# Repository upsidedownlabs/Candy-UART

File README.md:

# Candy UART

Candy size USB to UART bridge.

#### CH340C Candy

| Front              |  Back |
| :-------------------------: | :-------------------------: |
|   |  |

| Dimensions              |  Schematic |
| :-------------------------: | :-------------------------: |
| 24.00 x 17.00 mm  |  |

#### FT232RQ Candy

| Front              |  Back |
| :-------------------------: | :-------------------------: |
|   |  |

| Dimensions              |  Schematic |
| :-------------------------: | :-------------------------: |
| 24.00 x 17.00 mm  |  |

## License
#### Hardware
CERN Open Hardware License Version 2 - Strongly Reciprocal ([CERN-OHL-S-2.0](https://spdx.org/licenses/CERN-OHL-S-2.0.html)).

#### Software
MIT open source [license](http://opensource.org/licenses/MIT).

#### Documentation:
<br />This work is licensed under a <a rel="license" href="http://creativecommons.org/licenses/by/4.0/">Creative Commons Attribution 4.0 International License</a>.

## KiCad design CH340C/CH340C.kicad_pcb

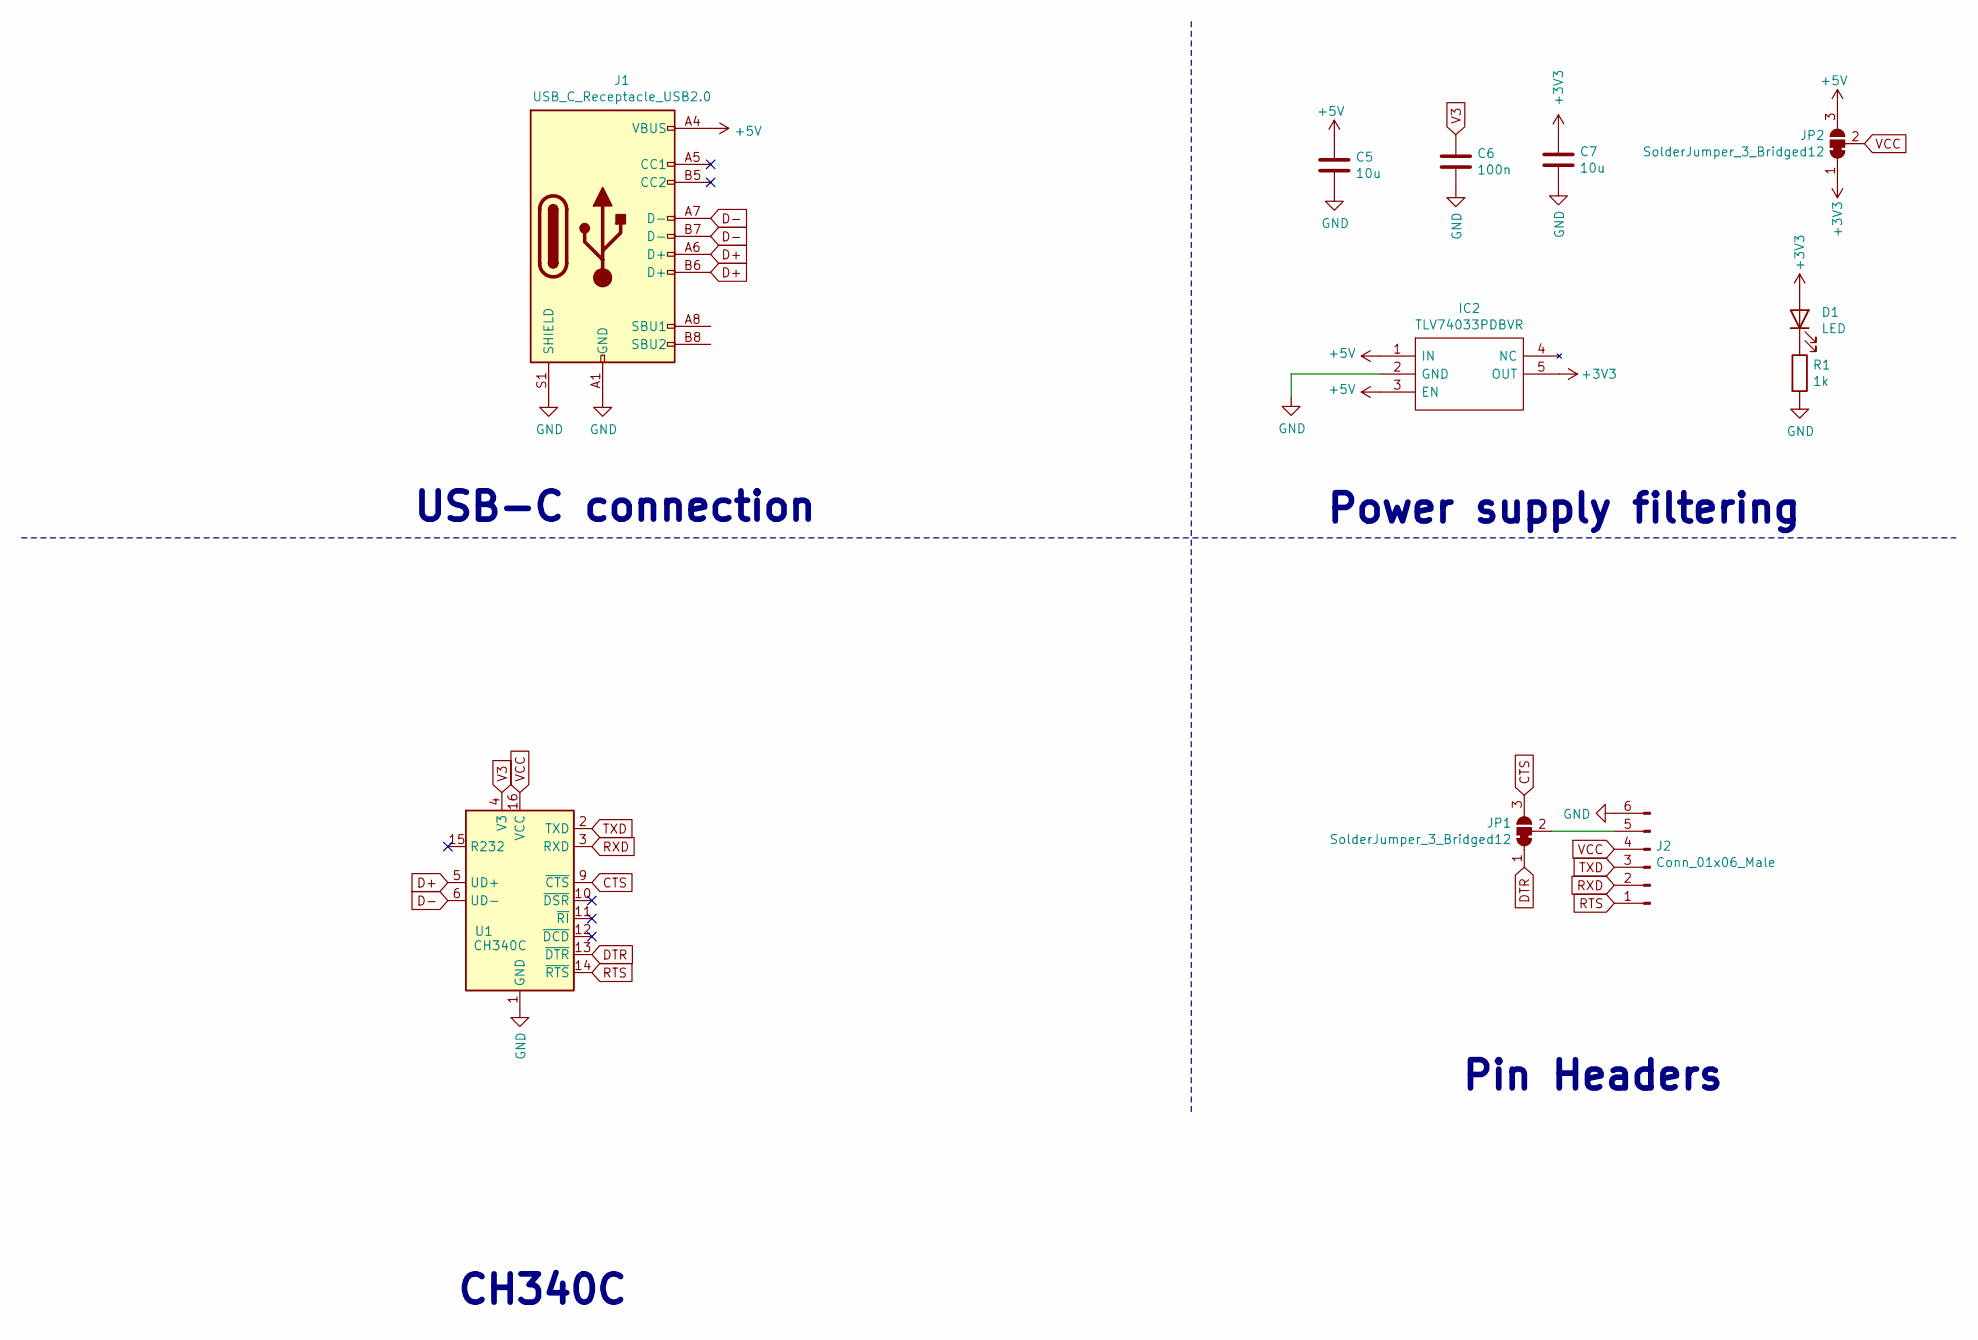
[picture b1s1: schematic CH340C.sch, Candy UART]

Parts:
C5, C7: 10u; C_0805_2012Metric_Pad1.18x1.45mm_HandSolder
C6: 100n; C_0805_2012Metric_Pad1.18x1.45mm_HandSolder
D1: LED; LED_0603_1608Metric_Pad1.05x0.95mm_HandSolder
IC2: TLV74033PDBVR; Manufacturer_Part_Number TLV74033PDBVR
J1: USB_C_Receptacle_USB2.0; USB_C_Receptacle_HRO_TYPE-C-31-M-12
J2: Conn_01x06_Male; PinSocket_1x06_P2.54mm_Vertical
JP1, JP2: SolderJumper_3_Bridged12; SolderJumper-3_P1.3mm_Bridged12_RoundedPad1.0x1.5mm
R1: 1k; R_0805_2012Metric_Pad1.20x1.40mm_HandSolder
U1: CH340C; SOIC-16_3.9x9.9mm_P1.27mm

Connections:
+3V3: C7.1, D1.2 (A), IC2.5 (OUT), JP2.1 (A)
+5V: C5.1, IC2.1 (IN), IC2.3 (EN), J1.A4 (VBUS), J1.A9 (VBUS), J1.B4 (VBUS), J1.B9 (VBUS), JP2.3 (B)
CTS: JP1.3 (B), U1.9 (~CTS)
D+: J1.A6 (D+), J1.B6 (D+), U1.5 (UD+)
D-: J1.A7 (D-), J1.B7 (D-), U1.6 (UD-)
DTR: JP1.1 (A), U1.13 (~DTR)
GND: C5.2, C6.2, C7.2, IC2.2 (GND), J1.A1 (GND), J1.A12 (GND), J1.B1 (GND), J1.B12 (GND), J1.S1 (SHIELD), J2.6, R1.2, U1.1 (GND)
unnamed: D1.1 (K), R1.1
unnamed: J2.5, JP1.2 (C)
RTS: J2.1, U1.14 (~RTS)
RXD: J2.2, U1.3 (RXD)
TXD: J2.3, U1.2 (TXD)
V3: C6.1, U1.4 (V3)
VCC: J2.4, JP2.2 (C), U1.16 (VCC)

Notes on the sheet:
Power supply filtering
USB-C connection
CH340C
Pin Headers

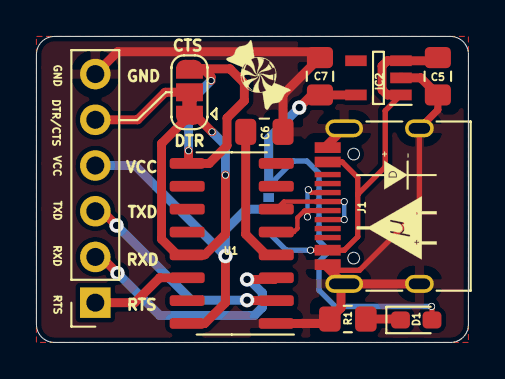
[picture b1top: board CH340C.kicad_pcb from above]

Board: 2 copper layers, 24.0 x 17.0 mm, 11 parts (1 on the bottom side), 14 nets.

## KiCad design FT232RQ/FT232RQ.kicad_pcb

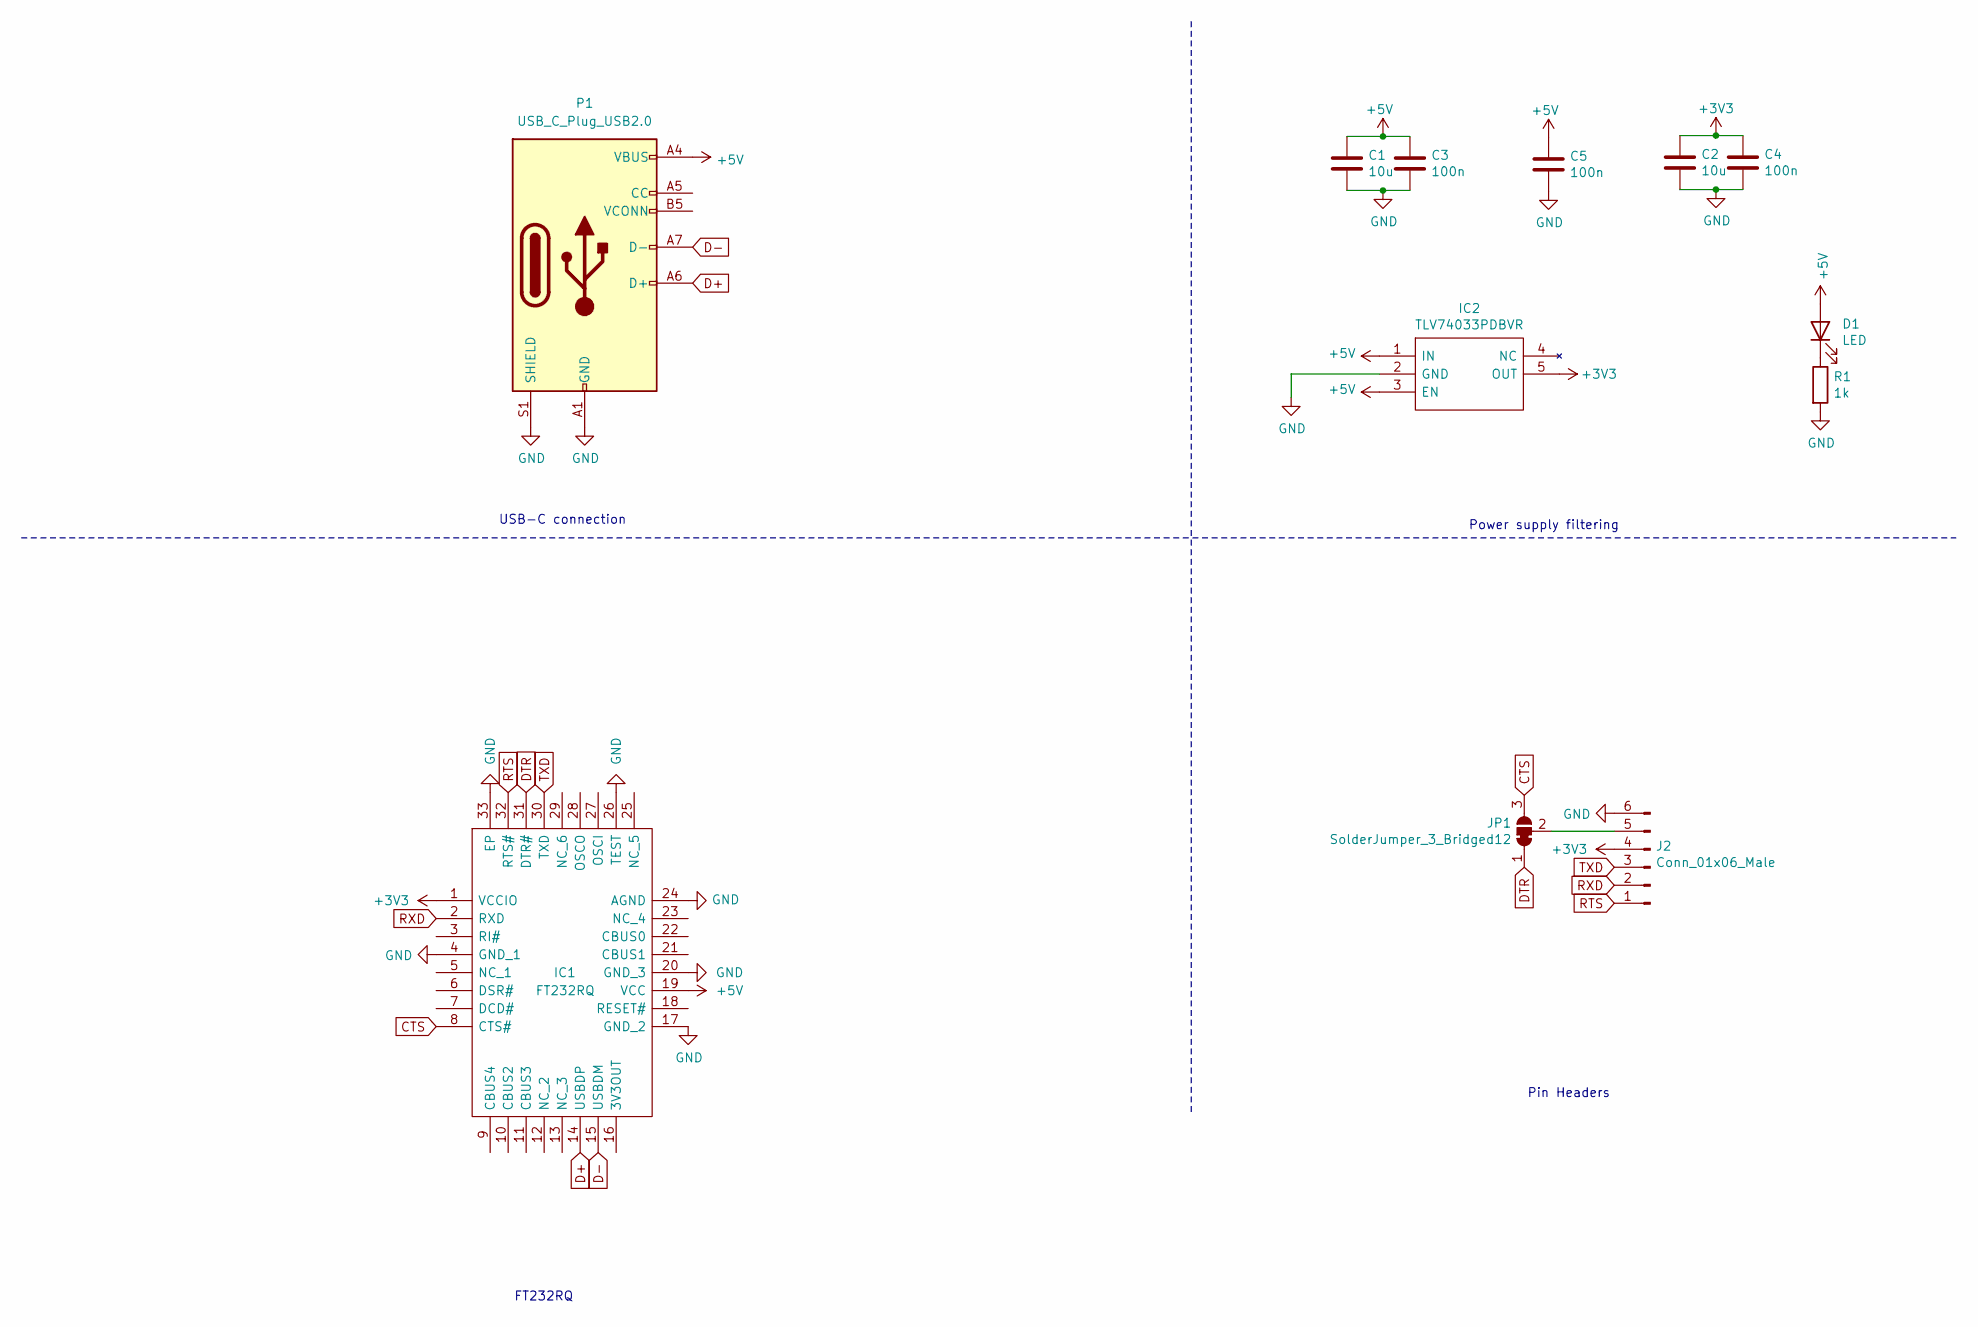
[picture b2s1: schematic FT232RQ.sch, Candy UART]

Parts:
C1, C2: 10u; C_1206_3216Metric_Pad1.33x1.80mm_HandSolder
C3, C4, C5: 100n; C_0805_2012Metric_Pad1.18x1.45mm_HandSolder
D1: LED; LED_0603_1608Metric_Pad1.05x0.95mm_HandSolder
IC1: FT232RQ; Manufacturer_Part_Number FT232RQ; Mouser Part Number 895-FT232RQ
IC2: TLV74033PDBVR; Manufacturer_Part_Number TLV74033PDBVR
J2: Conn_01x06_Male; PinSocket_1x06_P2.54mm_Vertical
JP1: SolderJumper_3_Bridged12; SolderJumper-3_P1.3mm_Bridged12_RoundedPad1.0x1.5mm
P1: USB_C_Plug_USB2.0; USB_C_Receptacle_HRO_TYPE-C-31-M-12
R1: 1k; R_0805_2012Metric_Pad1.20x1.40mm_HandSolder

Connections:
+3V3: C2.1, C4.1, IC1.1 (VCCIO), IC2.5 (OUT), J2.4
+5V: C1.1, C3.1, C5.1, D1.2 (A), IC1.19 (VCC), IC2.1 (IN), IC2.3 (EN), P1.A4 (VBUS), P1.A9 (VBUS), P1.B4 (VBUS), P1.B9 (VBUS)
CTS: IC1.8 (CTS#), JP1.3 (B)
D+: IC1.14 (USBDP), P1.A6 (D+)
D-: IC1.15 (USBDM), P1.A7 (D-)
DTR: IC1.31 (DTR#), JP1.1 (A)
GND: C1.2, C2.2, C3.2, C4.2, C5.2, IC1.4 (GND_1), IC1.17 (GND_2), IC1.20 (GND_3), IC1.24 (AGND), IC1.26 (TEST), IC1.33 (EP), IC2.2 (GND), J2.6, P1.A1 (GND), P1.A12 (GND), P1.B1 (GND), P1.B12 (GND), P1.S1 (SHIELD), R1.2
unnamed: D1.1 (K), R1.1
unnamed: J2.5, JP1.2 (C)
RTS: IC1.32 (RTS#), J2.1
RXD: IC1.2 (RXD), J2.2
TXD: IC1.30 (TXD), J2.3

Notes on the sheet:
Power supply filtering
USB-C connection
FT232RQ
Pin Headers

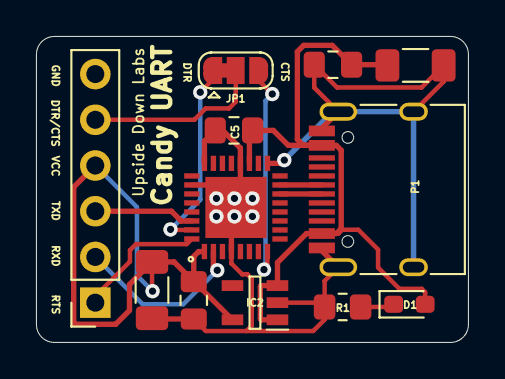
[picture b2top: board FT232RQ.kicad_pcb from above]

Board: 2 copper layers, 24.0 x 17.0 mm, 12 parts (0 on the bottom side), 12 nets.

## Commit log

2021-01-28 Add KiCAD files
    KiCAD files for Candy UART (FT232RQ variant).
2021-01-28 add FT232RQ schematic
    Schematic for FT232RQ based Candy UART board from Upside Down Labs.
2021-01-28 add FT232RQ back image
    Rendered back image of FT232RQ based Candy UART board.
2021-01-28 add FT232RQ front image
    Rendered front image of FT232RQ based Candy UART board.
2021-01-28 add FT232RQ dimensions image
    Rendered dimensions image of FT232RQ based Candy UART board.
2021-01-28 update FT232RQ back image
    The normal image replaced with image captured with raytracing feature of KiCAD.
2021-01-29 update PCB
    tracks has been rerouted to make sure nobody cuts when manipulating the solder joint.
2021-01-29 update images
2021-01-30 Update License
2021-01-30 add FT232RQ schematic image
2021-01-30 resize FT232RQ dimensions image
2021-02-04 Add Ch340C candy
2021-02-04 ignore 3D files
2021-02-04 Ch340C candy back
2021-02-04 Ch340C candy front
2021-02-04 add Ch340C candy schematic image
2021-02-04 add Ch340C candy dimensions image
2021-02-04 rotate FT232RQ candy schematic image
2021-02-04 add CH340C schematic pdf
2021-02-04 update to CH340C v0.4 back
2021-02-04 update to CH340C v0.4 dimensions
2021-02-04 update to CH340C v0.4 front
2021-02-04 update to CH340C v0.4 schematic
2021-02-18 Update CH340C schematic pdf
2021-02-18 Update CH340C schematic
